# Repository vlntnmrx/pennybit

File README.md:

# PennyBIT

This borad is a very stripped-down feather style bord using a Cortex-M0 by ST. The main goal was to create a board with a BOM <$2.5 to use in everyday projects while still preserving the key functions of a Adafruit(R) Feather, like the LiPo Charger and the pinout. As a bonus, three of the pins are driven by MOSFETs e.g. to allow the use of RBG LED strips.

## Tech Spec
* STM32F042K6T Microcontroller
* MCP73831 LiPo Charger
* Built in USB-bootloader
* Access to SWD port
* Boot button, usable as user input in normal operation
* Pin compatible to Adafruit(R) Feather

## Current state
First batch is assembled and tested. No Problems found (yet) :smile:

### Note
The project was originally called "cheapFeather" so some files still carry this name.

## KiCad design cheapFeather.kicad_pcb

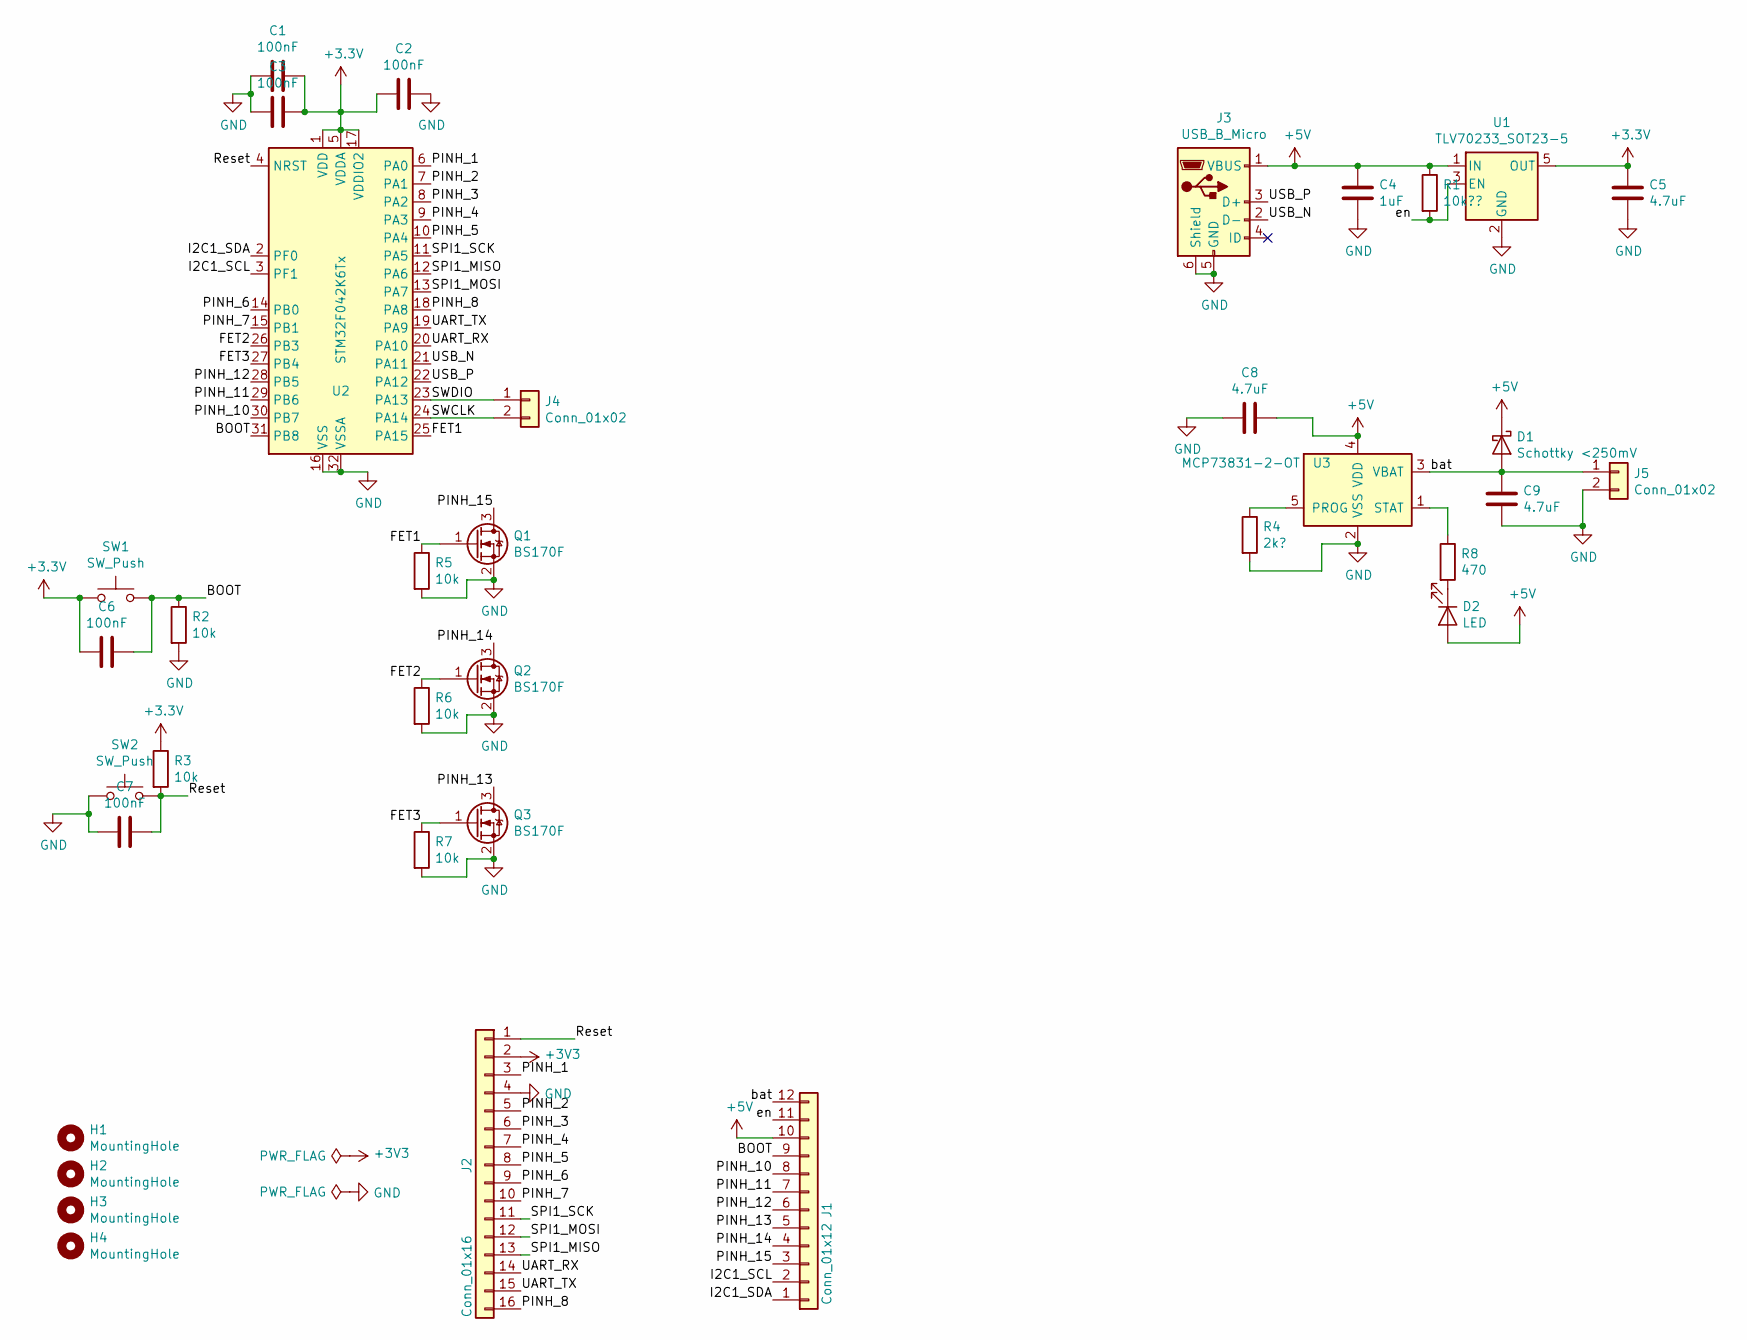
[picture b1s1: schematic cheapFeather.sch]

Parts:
C1, C2, C3, C6, C7: 100nF; C_0805_2012Metric
C4: 1uF; C_0805_2012Metric
C5, C8, C9: 4.7uF; C_0805_2012Metric
D1: Schottky <250mV; D_SOD-123
D2: LED; LED_0805_2012Metric
H1, H2, H3, H4: MountingHole; MountingHole_2.7mm_M2.5
J1: Conn_01x12; PinHeader_1x12_P2.54mm_Vertical
J2: Conn_01x16; PinHeader_1x16_P2.54mm_Vertical
J3: USB_B_Micro; USB_Micro_XKB
J4: Conn_01x02; PinHeader_1x02_P2.54mm_Vertical
J5: Conn_01x02; JST_PH_S2B-PH-K_1x02_P2.00mm_Horizontal
Q1, Q2, Q3: BS170F; SOT-23
R1: 10k??; R_0805_2012Metric
R2, R3, R5, R6, R7: 10k; R_0805_2012Metric
R4: 2k?; R_0805_2012Metric
R8: 470; R_0805_2012Metric
SW1, SW2: SW_Push; SW_SPST_PTS810
U1: TLV70233_SOT23-5; SOT-23-5
U2: STM32F042K6Tx; LQFP-32_7x7mm_P0.8mm
U3: MCP73831-2-OT; SOT-23-5

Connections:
+5V: C4.1, C8.1, D1.1 (K), D2.2 (A), J1.10, J3.1 (VBUS), R1.1, U1.1 (IN), U3.4 (VDD)
/BOOT: C6.1, J1.9, R2.1, SW1.2, U2.31 (PB8)
/FET1: Q1.1 (G), R5.1, U2.25 (PA15)
/FET2: Q2.1 (G), R6.1, U2.26 (PB3)
/FET3: Q3.1 (G), R7.1, U2.27 (PB4)
/I2C1_SCL: J1.2, U2.3 (PF1)
/I2C1_SDA: J1.1, U2.2 (PF0)
/PINH_1: J2.3, U2.6 (PA0)
/PINH_2: J2.5, U2.7 (PA1)
/PINH_3: J2.6, U2.8 (PA2)
/PINH_4: J2.7, U2.9 (PA3)
/PINH_5: J2.8, U2.10 (PA4)
/PINH_6: J2.9, U2.14 (PB0)
/PINH_7: J2.10, U2.15 (PB1)
/PINH_8: J2.16, U2.18 (PA8)
/PINH_10: J1.8, U2.30 (PB7)
/PINH_11: J1.7, U2.29 (PB6)
/PINH_12: J1.6, U2.28 (PB5)
/PINH_13: J1.5, Q3.3 (D)
/PINH_14: J1.4, Q2.3 (D)
/PINH_15: J1.3, Q1.3 (D)
/Reset: C7.1, J2.1, R3.2, SW2.2, U2.4 (NRST)
/SPI1_MISO: J2.13, U2.12 (PA6)
/SPI1_MOSI: J2.12, U2.13 (PA7)
/SPI1_SCK: J2.11, U2.11 (PA5)
/SWCLK: J4.2, U2.24 (PA14)
/SWDIO: J4.1, U2.23 (PA13)
/UART_RX: J2.14, U2.20 (PA10)
/UART_TX: J2.15, U2.19 (PA9)
/USB_N: J3.2 (D-), U2.21 (PA11)
/USB_P: J3.3 (D+), U2.22 (PA12)
/bat: C9.1, D1.2 (A), J1.12, J5.1, U3.3 (VBAT)
/en: J1.11, R1.2, U1.3 (EN)
GND: C1.2, C2.1, C3.2, C4.2, C5.2, C7.2, C8.2, C9.2, J2.4, J3.5 (GND), J3.6 (Shield), J5.2, Q1.2 (S), Q2.2 (S), Q3.2 (S), R2.2, R4.2, R5.2, R6.2, R7.2, SW2.1, U1.2 (GND), U2.16 (VSS), U2.32 (VSSA), U3.2 (VSS)
unnamed: D2.1 (K), R8.2
unnamed: R4.1, U3.5 (PROG)
unnamed: R8.1, U3.1 (STAT)

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
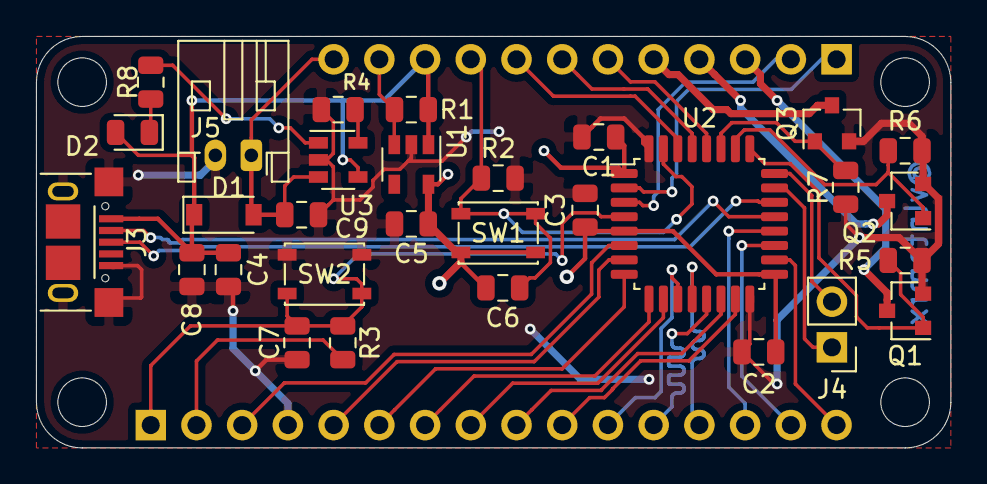
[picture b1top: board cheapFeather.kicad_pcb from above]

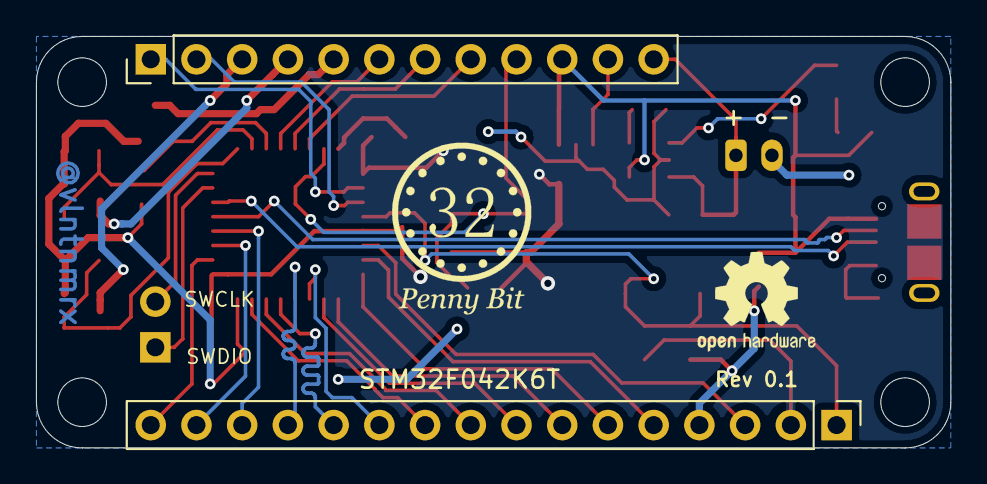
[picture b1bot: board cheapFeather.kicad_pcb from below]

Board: 2 copper layers, 50.8 x 22.9 mm, 36 parts (2 on the bottom side), 38 nets.

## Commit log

2020-10-09 Init Commit
2020-10-12 Changed cap. values
